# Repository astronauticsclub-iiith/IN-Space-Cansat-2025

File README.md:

## INSpace CanSat 24-25.

We have open-sourced our codefiles, 3D CAD models, PCB designs and simulation code for future teams participating in team in CanSat or anyone interested. The mission requirements for INSpace CanSat 24-25 be found [here](/Mission_Requirements). The directory structure is mostly self-explanatory.

**Team Name:** Team Brahmand (IIIT Hyderabad)

**Sponsors:** iHub Data (prototyping and development cost), IIIT Hyderabad (travel support)

**Advisor:** Prof Harikumar Kandath and Prof. Kavita Vemuri

**Members:** 
- Harsh Kapoor (Team Lead)
- Madhan Sai Krishna
- Vignesh Vembar
- Vijay Aravynthan S R
- Anushka Sharma
- Tejasvini Ramaswamy

**Additional Contributors:**
- Nav Singhal
- Kandagatla Akshith
- Tatva Agarwal
- Akshat Puneet
- Srinath Dhatre
- Bhaskar Itikela

**Mentors:** Members of Team Wanderlust (represented IIIT Hyderabad in US CanSat 23-24)

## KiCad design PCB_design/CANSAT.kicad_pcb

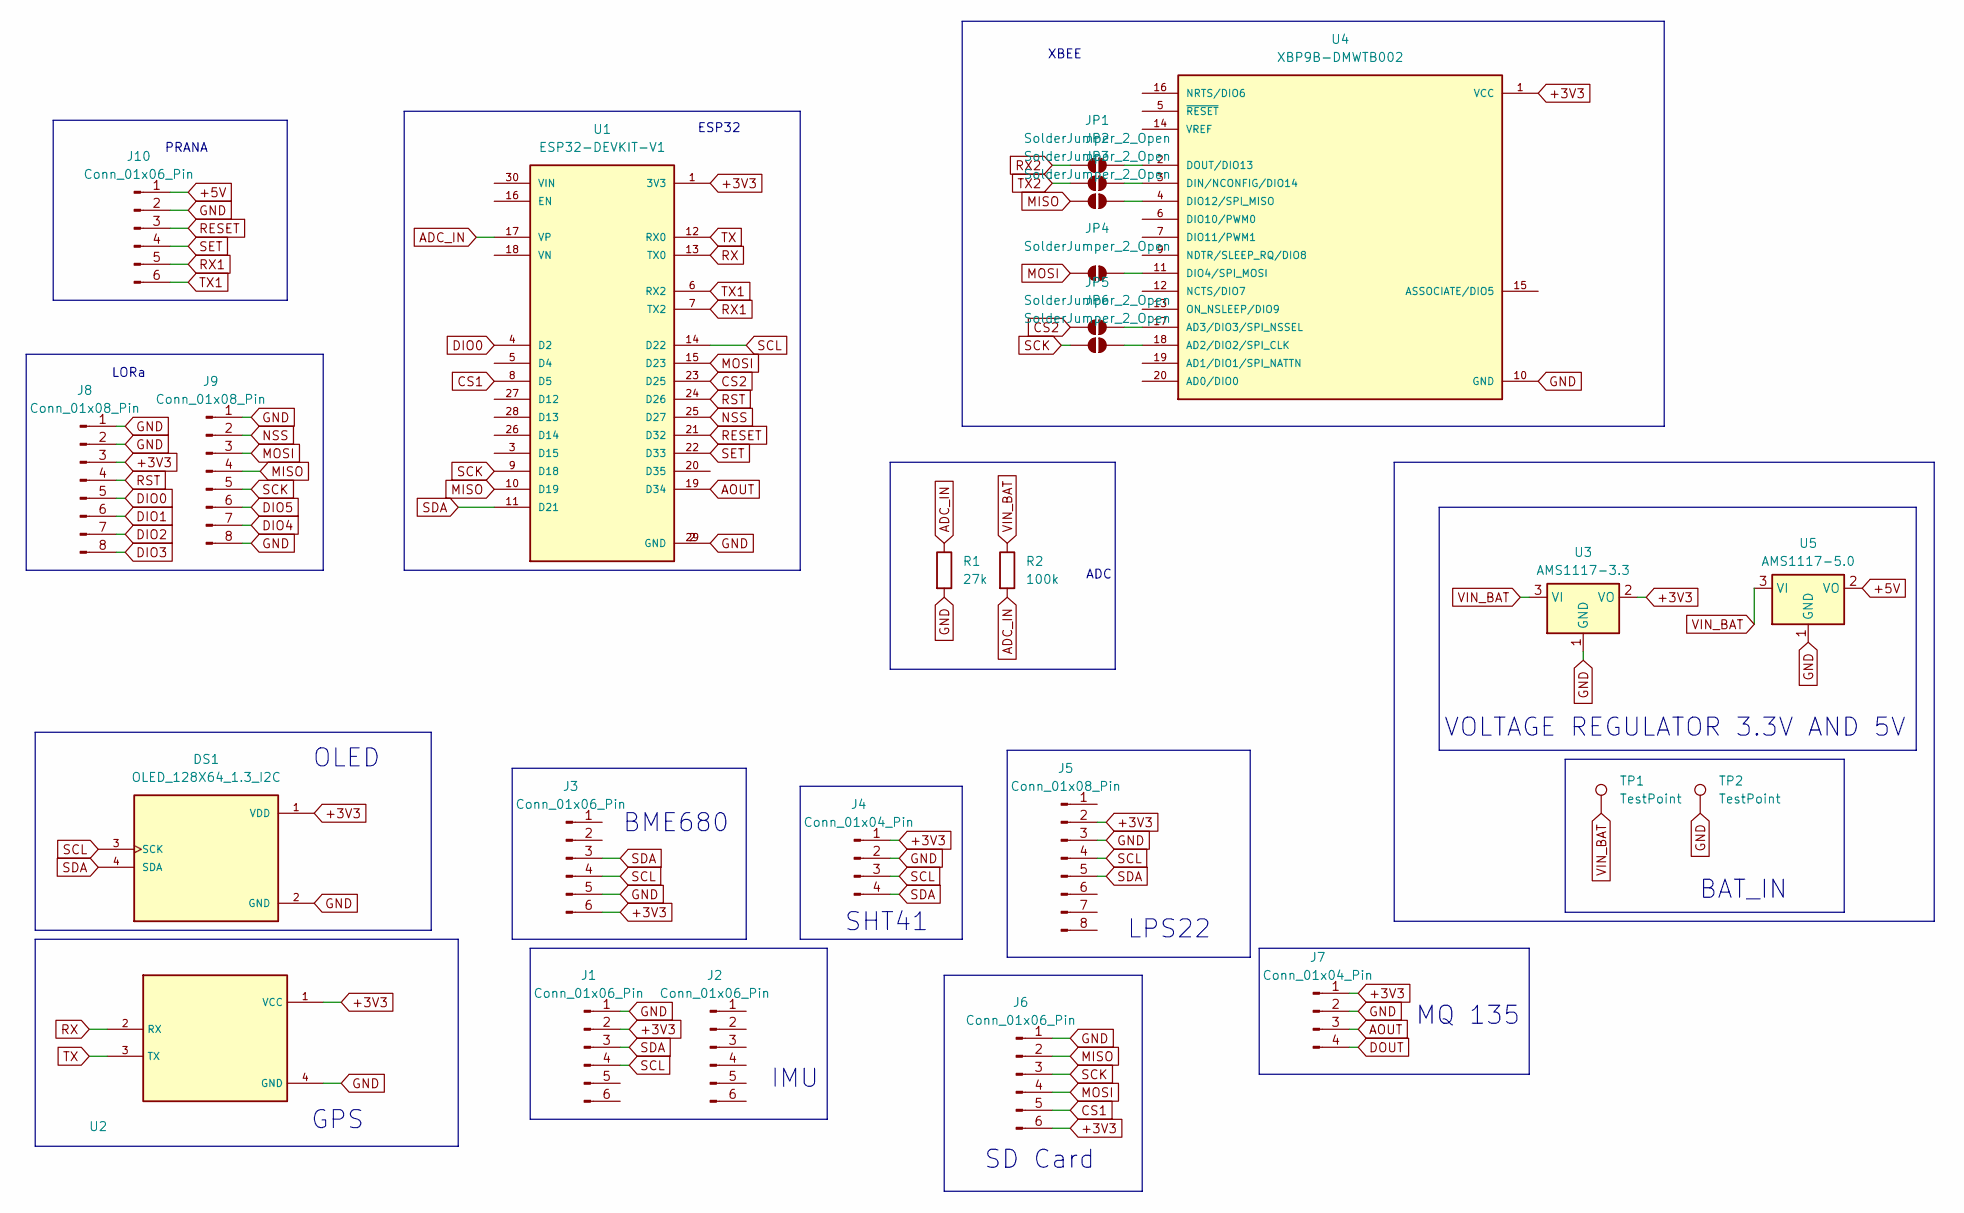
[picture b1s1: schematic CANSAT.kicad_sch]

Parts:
DS1: OLED_128X64_1.3_I2C; LCD_OLED_128X64_1.3_I2C; PARTREV NA
J1, J2, J3, J6, J10: Conn_01x06_Pin; PinSocket_1x06_P2.54mm_Vertical
J4, J7: Conn_01x04_Pin; PinSocket_1x04_P2.54mm_Vertical
J5, J8, J9: Conn_01x08_Pin; PinHeader_1x08_P2.54mm_Vertical
JP1, JP2, JP3, JP4, JP5, JP6: SolderJumper_2_Open; SolderJumper-2_P1.3mm_Open_TrianglePad1.0x1.5mm
R1: 27k; R_Axial_DIN0411_L9.9mm_D3.6mm_P15.24mm_Horizontal
R2: 100k; R_Axial_DIN0411_L9.9mm_D3.6mm_P15.24mm_Horizontal
TP1, TP2: TestPoint; TestPoint_Pad_4.0x4.0mm
U1: ESP32-DEVKIT-V1; MODULE_ESP32_DEVKIT_V1; PARTREV N/A
U2: NEO_GPS
U3: AMS1117-3.3; SOT-223-3_TabPin2
U4: XBP9B-DMWTB002; DIP2200W51P200L3294H279Q20P
U5: AMS1117-5.0; SOT-223-3_TabPin2

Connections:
+3V3: DS1.1 (VDD), J1.2, J3.6, J4.1, J5.2, J6.6, J7.1, J8.3, U1.1 (3V3), U2.1 (VCC), U3.2 (VO), U4.1 (VCC)
+5V: J10.1, U5.2 (VO)
ADC_IN: R1.1, R2.2, U1.17 (VP)
AOUT: J7.3, U1.19 (D34)
CS1: J6.5, U1.8 (D5)
CS2: JP5.1 (A), U1.23 (D25)
D4: U1.5 (D4); also elsewhere on the board
D12: U1.27 (D12); also elsewhere on the board
D13: U1.28 (D13); also elsewhere on the board
D14: U1.26 (D14); also elsewhere on the board
D15: U1.3 (D15); also elsewhere on the board
DIO0: J8.5, U1.4 (D2)
DIO1: J8.6
DIO2: J8.7
DIO3: J8.8
DIO4: J9.7
DIO5: J9.6
DOUT: J7.4
EN: U1.16 (EN); also elsewhere on the board
GND: DS1.2 (GND), J1.1, J3.5, J4.2, J5.3, J6.1, J7.2, J8.1, J8.2, J9.1, J9.8, J10.2, R1.2, TP2.1, U1.2 (GND), U1.29 (GND), U2.4 (GND), U3.1 (GND), U4.10 (GND), U5.1 (GND)
MISO: J6.2, J9.4, JP3.1 (A), U1.10 (D19)
MOSI: J6.4, J9.3, JP4.1 (A), U1.15 (D23)
NSS: J9.2, U1.25 (D27)
unnamed: JP1.2 (B), U4.2 (DOUT/DIO13)
unnamed: JP2.2 (B), U4.3 (DIN/NCONFIG/DIO14)
unnamed: JP3.2 (B), U4.4 (DIO12/SPI_MISO)
unnamed: JP4.2 (B), U4.11 (DIO4/SPI_MOSI)
unnamed: JP5.2 (B), U4.17 (AD3/DIO3/SPI_NSSEL)
unnamed: JP6.2 (B), U4.18 (AD2/DIO2/SPI_CLK)
RESET: J10.3, U1.21 (D32)
RST: J8.4, U1.24 (D26)
RX: U1.13 (TX0), U2.2 (RX)
RX1: J10.5, U1.7 (TX2)
RX2: JP1.1 (A)
SCK: J6.3, J9.5, JP6.1 (A), U1.9 (D18)
SCL: DS1.3 (SCK), J1.4, J3.4, J4.3, J5.4, U1.14 (D22)
SDA: DS1.4 (SDA), J1.3, J3.3, J4.4, J5.5, U1.11 (D21)
SET: J10.4, U1.22 (D33)
TX: U1.12 (RX0), U2.3 (TX)
TX1: J10.6, U1.6 (RX2)
TX2: JP2.1 (A)
VIN: U1.30 (VIN); also elsewhere on the board
VIN_BAT: R2.1, TP1.1, U3.3 (VI), U5.3 (VI)
VN: U1.18 (VN); also elsewhere on the board

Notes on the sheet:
OLED
SD Card
BAT_IN
LPS22
XBEE
ESP32
SHT41
IMU
GPS
VOLTAGE REGULATOR 3.3V AND 5V
ADC
PRANA
BME680
LORa
MQ 135

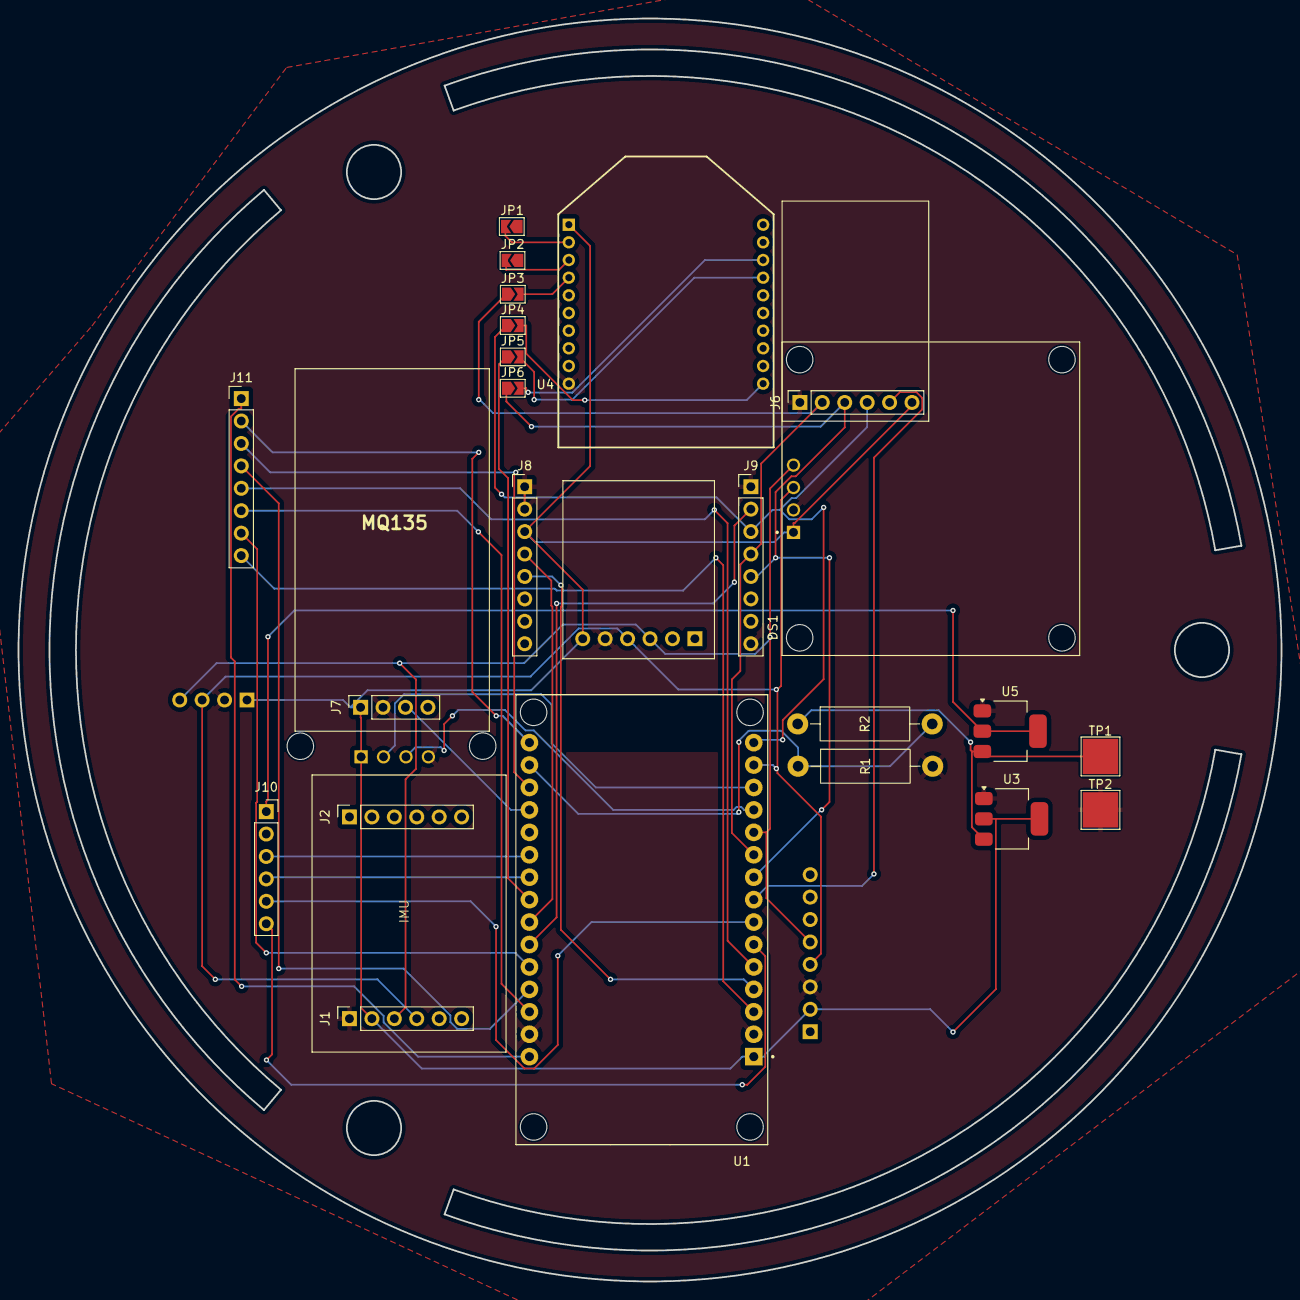
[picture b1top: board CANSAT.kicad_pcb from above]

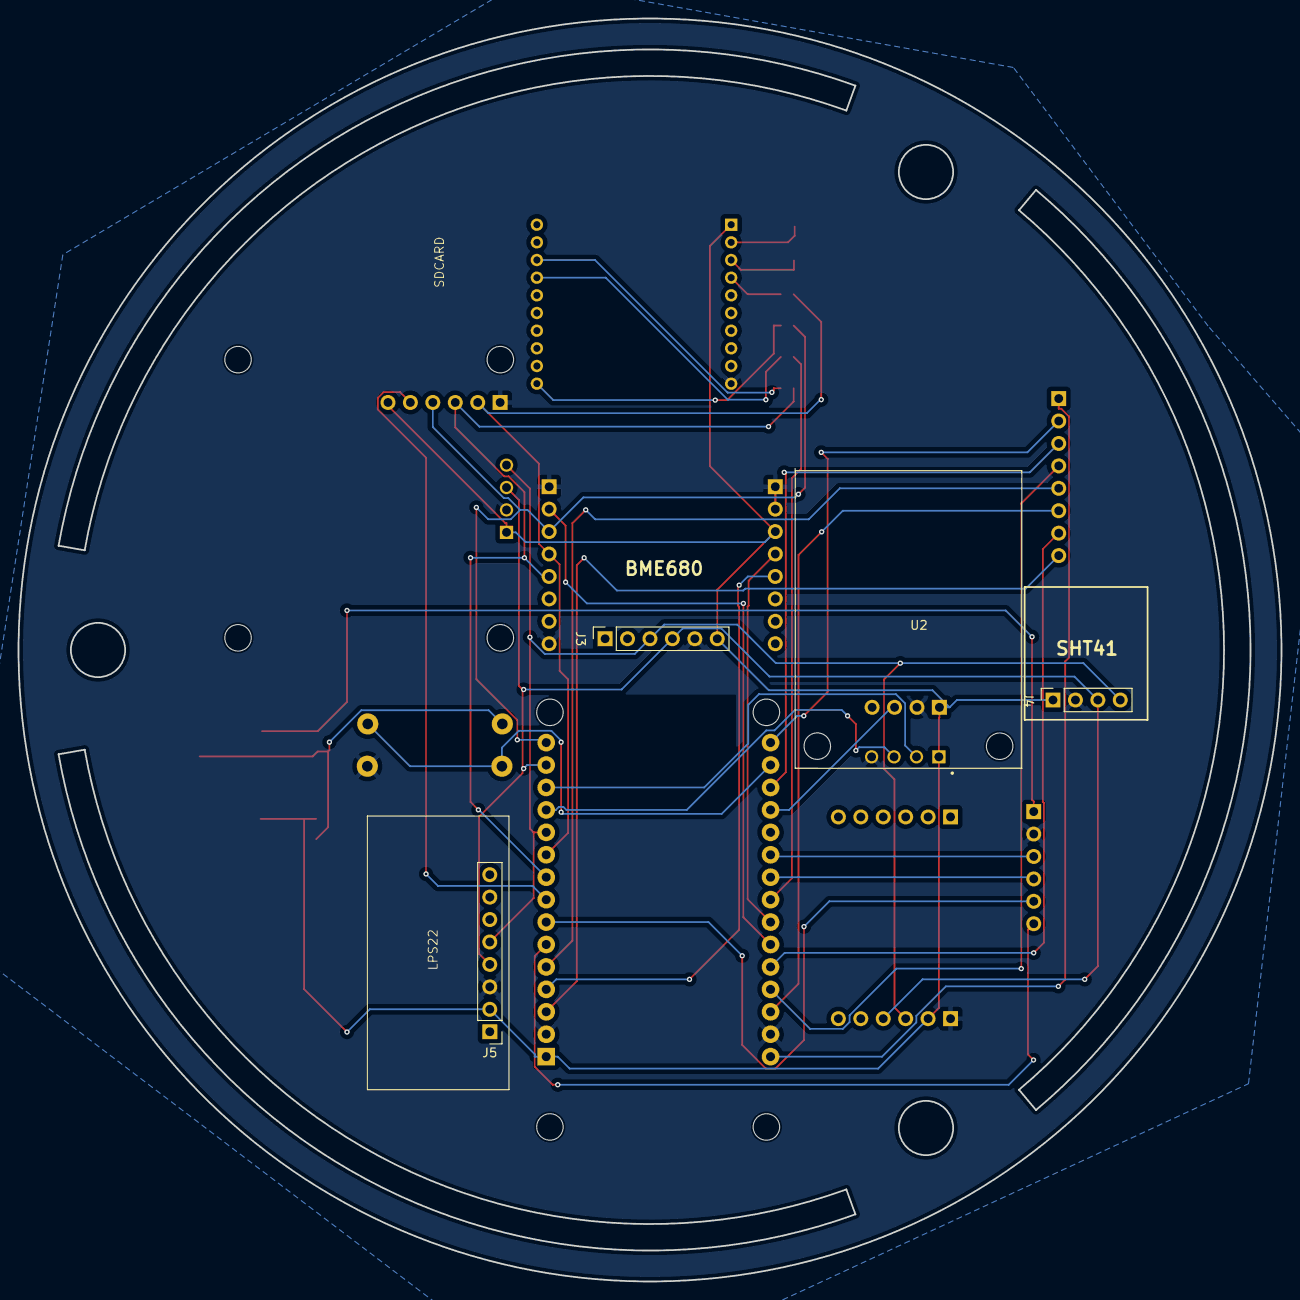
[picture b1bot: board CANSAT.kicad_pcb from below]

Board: 2 copper layers, 143.0 x 143.0 mm, 27 parts (4 on the bottom side), 36 nets.

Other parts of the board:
J11: Conn_01x08_Pin; PinHeader_1x08_P2.54mm_Vertical

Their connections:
D4: J11.5; also elsewhere on the board
D12: J11.4; also elsewhere on the board
D13: J11.6; also elsewhere on the board
D14: J11.7; also elsewhere on the board
D15: J11.8; also elsewhere on the board
EN: J11.2; also elsewhere on the board
VIN: J11.1; also elsewhere on the board
VN: J11.3; also elsewhere on the board

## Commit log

2025-11-05 Added git ignore
2025-11-05 Updated git ignore
2025-11-05 Added all files
2025-11-13 Added cad files
2025-11-13 Added the Data collection files
    Data collected during CanSat launch.
2025-12-01 Added pcb design files
2025-12-01 Added mission requirement guidelines
2025-12-01 Added reports
2025-12-01 Added README.md
